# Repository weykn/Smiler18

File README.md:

# Smiler18: 18-Key Keyboard

The **Smiler18** is a custom 18-key keyboard featuring hotswap low-profile switches. This project provides everything you need to build your own Smiler18 keyboard.

## Features
- **18 Keys**
- **Hotswap Sockets**
- **Kalih Low Profile Switches**
- **RP2040 Zero**
- **VIAL or QMK Firmware**

## Requirements
To build the Smiler18, you will need the following components:
- **1x RP2040 Zero** ([link](https://de.aliexpress.com/item/1005005106645508.html?spm=a2g0o.order_list.order_list_main.79.126b5c5fcnu92V&gatewayAdapt=glo2deu))
- **18x Kalih Choc Hotswap Sockets** ([link](https://de.aliexpress.com/item/1005006610506123.html?spm=a2g0o.order_list.order_list_main.33.451d5c5f76XTpe&gatewayAdapt=glo2deu))
- **18x Kalih Choc Switches**
- **18x Keycaps for Kalih Choc Switches**
- **(Optional) Sockets for MCU** ([link](https://de.aliexpress.com/item/4001122376295.html?spm=a2g0o.order_list.order_list_main.119.46335c5fZQ0dM3&gatewayAdapt=glo2deu))
- **(Optional) Silicone Bumpers** ([link](https://de.aliexpress.com/item/1005002619943801.html?spm=a2g0o.order_list.order_list_main.124.46335c5fZQ0dM3&gatewayAdapt=glo2deu))
- Soldering equipment and materials

## Files
You can find the necessary files for this project in the [Releases](https://github.com/weykn/Smiler18/releases/tag/main)
- **Gerber File**: For PCB manufacturing.
- **UF2 File**: For flashing the firmware onto the RP2040 Zero.
- **VIL File**: VIAL config.

## Images

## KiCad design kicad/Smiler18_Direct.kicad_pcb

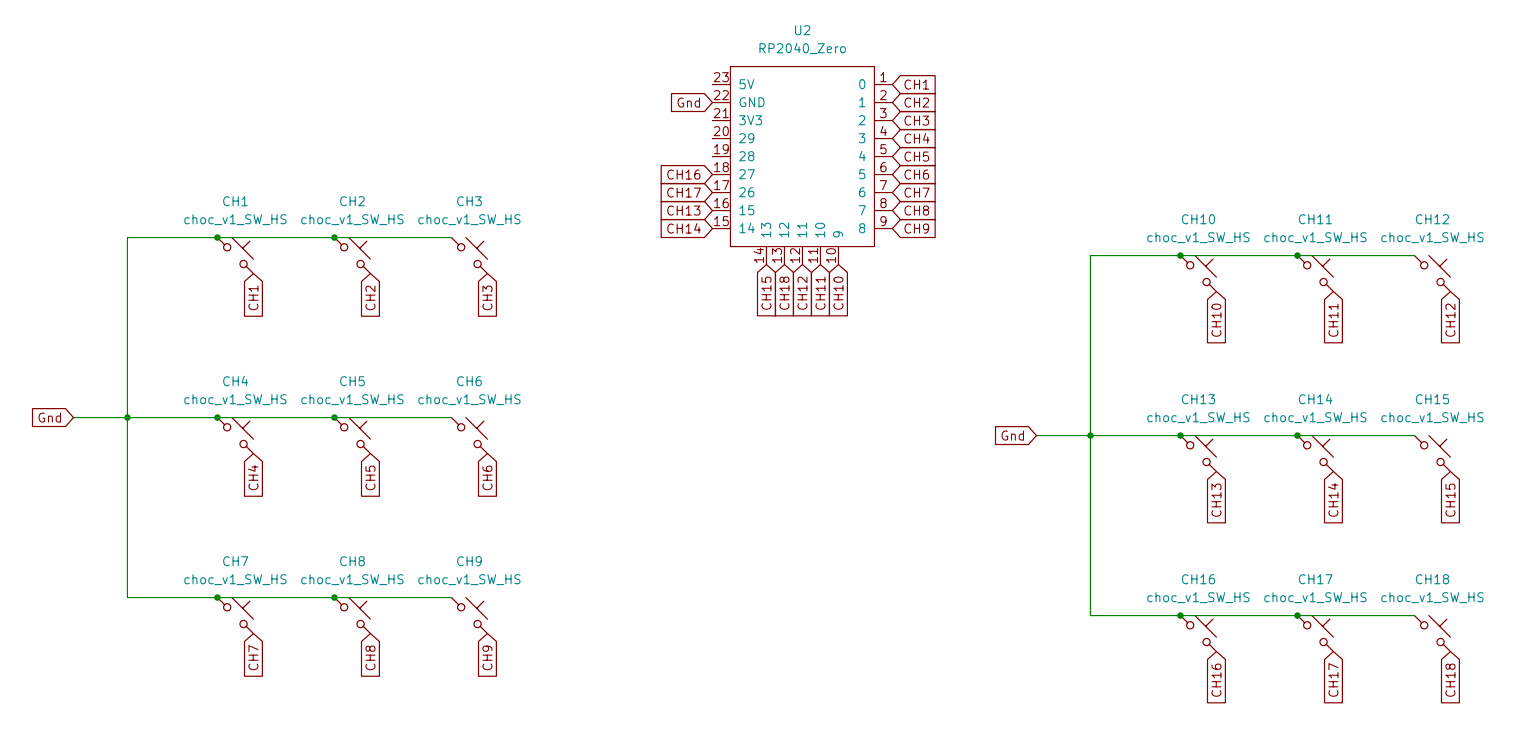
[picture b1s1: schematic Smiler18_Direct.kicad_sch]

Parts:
CH1, CH2, CH3, CH4, CH5, CH6, CH7, CH8, CH9, CH10, CH11, CH12, CH13, CH14, CH15, CH16, CH17, CH18: choc_v1_SW_HS; SW_choc_v1_HS_CPG135001S30_1u
U2: RP2040_Zero

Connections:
CH1: CH1.2, U2.1 (0)
CH2: CH2.2, U2.2 (1)
CH3: CH3.2, U2.3 (2)
CH4: CH4.2, U2.4 (3)
CH5: CH5.2, U2.5 (4)
CH6: CH6.2, U2.6 (5)
CH7: CH7.2, U2.7 (6)
CH8: CH8.2, U2.8 (7)
CH9: CH9.2, U2.9 (8)
CH10: CH10.2, U2.10 (9)
CH11: CH11.2, U2.11 (10)
CH12: CH12.2, U2.12 (11)
CH13: CH13.2, U2.16 (15)
CH14: CH14.2, U2.15 (14)
CH15: CH15.2, U2.14 (13)
CH16: CH16.2, U2.18 (27)
CH17: CH17.2, U2.17 (26)
CH18: CH18.2, U2.13 (12)
Gnd: CH1.1, CH2.1, CH3.1, CH4.1, CH5.1, CH6.1, CH7.1, CH8.1, CH9.1, CH10.1, CH11.1, CH12.1, CH13.1, CH14.1, CH15.1, CH16.1, CH17.1, CH18.1, U2.22 (GND)

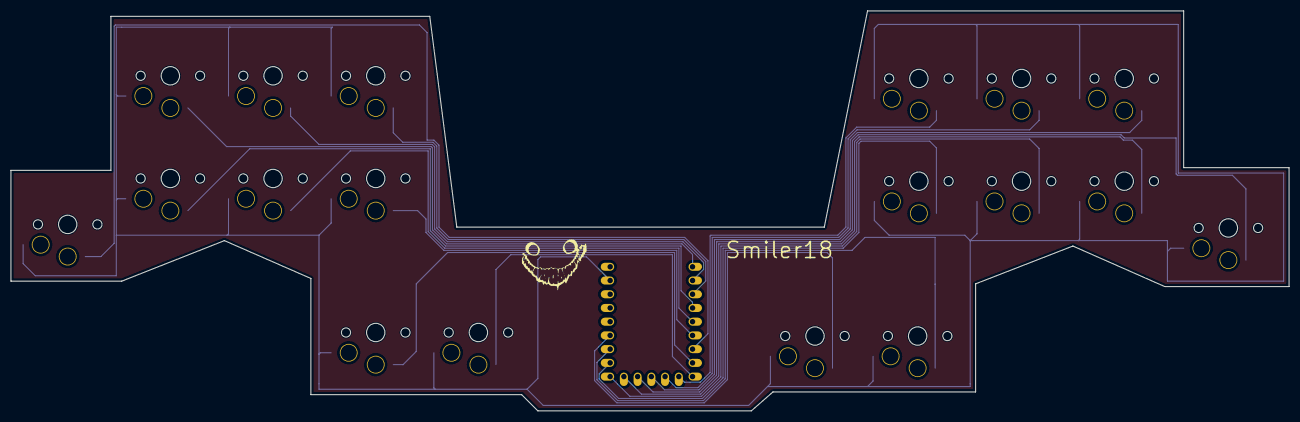
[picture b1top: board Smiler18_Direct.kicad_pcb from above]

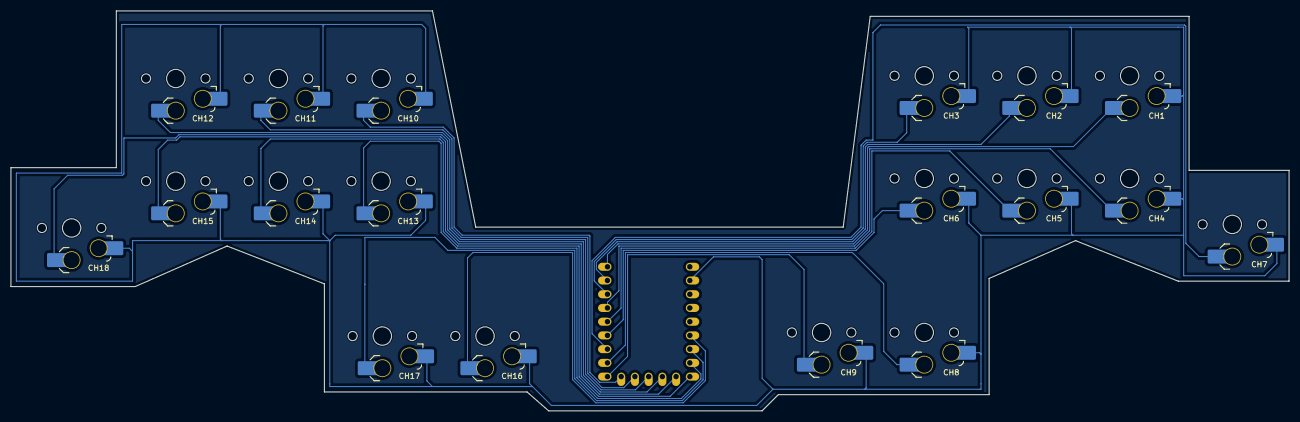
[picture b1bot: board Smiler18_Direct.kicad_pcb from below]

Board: 2 copper layers, 236.5 x 74.0 mm, 19 parts (18 on the bottom side), 19 nets.

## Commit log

2024-07-19 init
2024-07-19 done
2024-07-19 vial
2024-07-25 keymap
2024-07-29 mcu led
